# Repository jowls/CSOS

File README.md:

# csos

Current sink PCB for battery testing. Designed in KiCad. Includes circuit simulation (LTspice) and GERBER manufacturing files (configured for OSH Park fab). Studying Contextual Electronics courseware.

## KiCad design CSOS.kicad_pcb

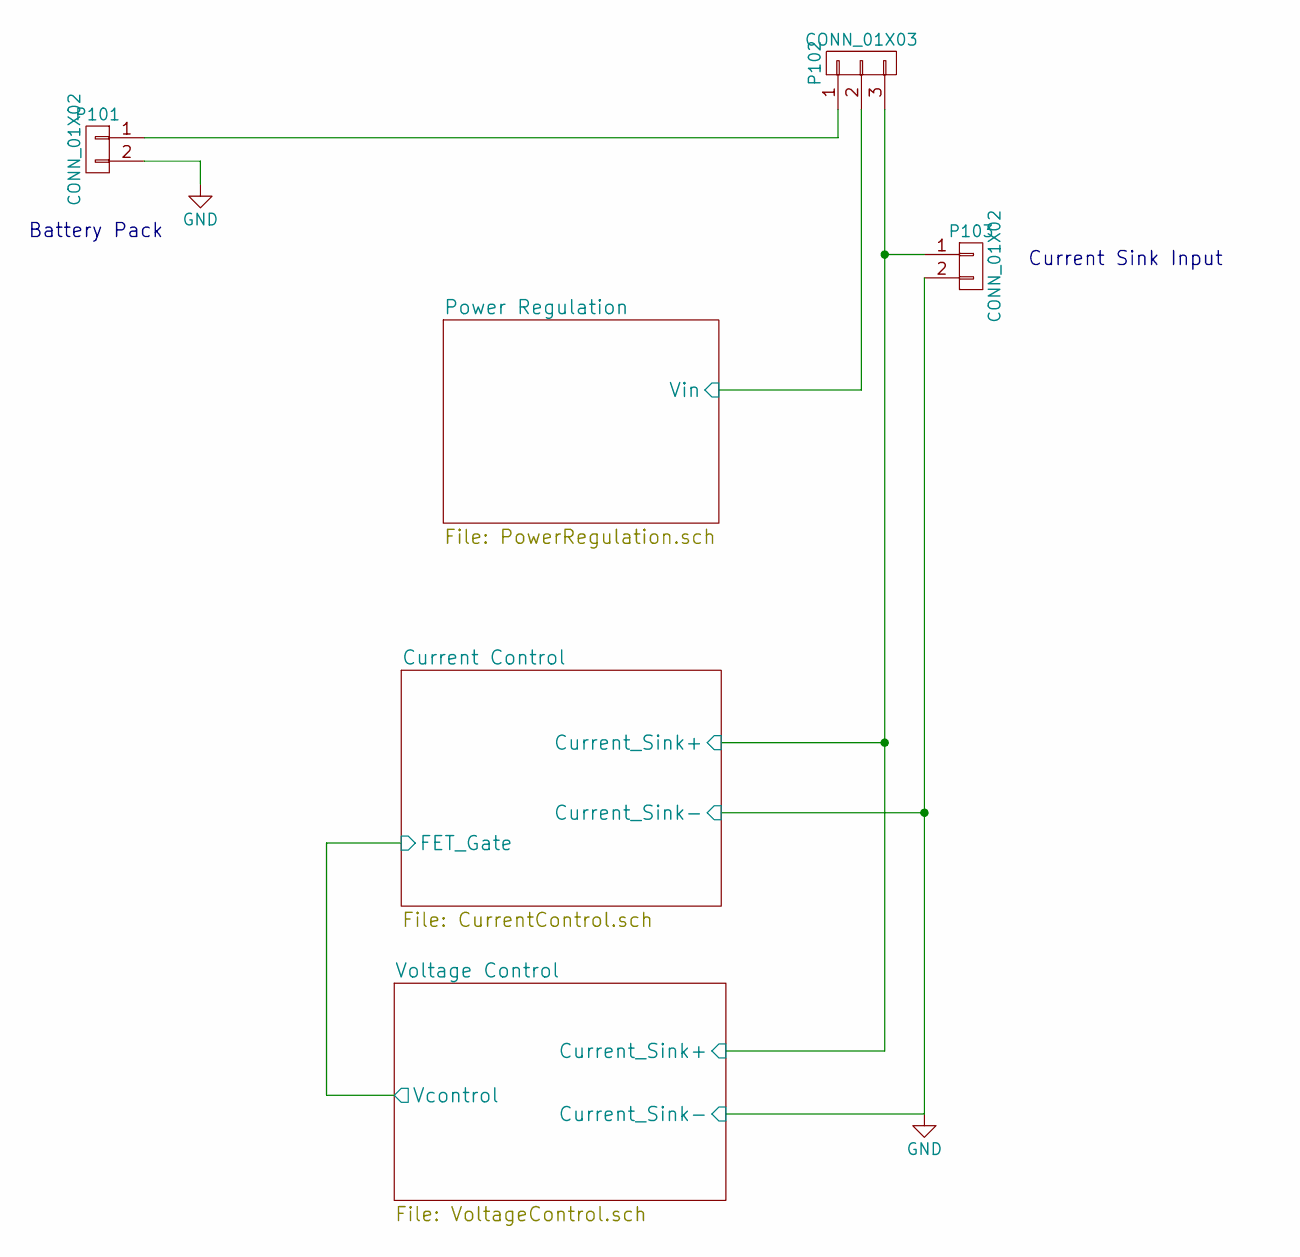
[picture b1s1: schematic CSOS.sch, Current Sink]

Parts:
P101, P103: CONN_01X02; Terminal_Block_200_mil; MPN OSTTC022162
P102: CONN_01X03; Pin_Header_Straight_1x03; MPN M20-9990346

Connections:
/Current Control/Current_Sink+: P102.3, P103.1; also elsewhere on the board
/Power Regulation/Vin: P102.2; also elsewhere on the board
GND: P101.2, P103.2; also elsewhere on the board
unnamed: P101.1, P102.1

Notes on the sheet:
Battery Pack
Current Sink Input

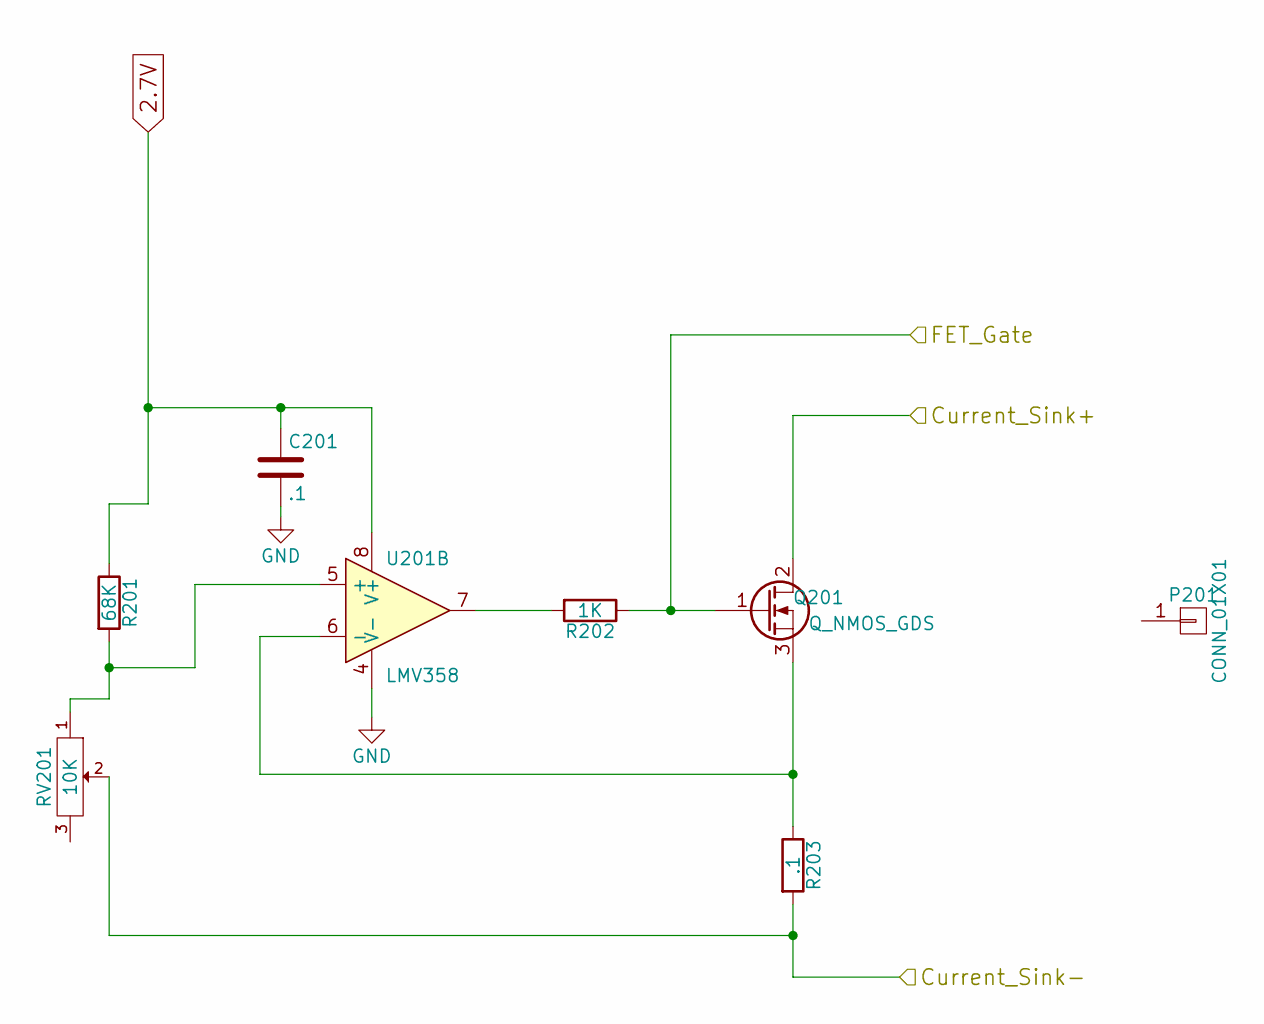
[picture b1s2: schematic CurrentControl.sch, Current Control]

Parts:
C201: .1; C_0805_HandSoldering; MPN 08055C104KAT2A
P201: CONN_01X01; FA-T220-38E; MPN FA-T220-38E
Q201: Q_NMOS_GDS; TO-220_Neutral123_Vertical; MPN PHP23NQ11T,127
R201: 68K; R_0805_HandSoldering
R202: 1K; R_0805_HandSoldering
R203: .1; Resistor_Horizontal_RM15mm; MPN AC01000001007JA100
RV201: 10K; P090L-02F25BR10K; MPN P090L-02F25BR10K
U201: LMV358; SOIC-8-N; MPN LMV358IDT

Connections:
2.7V: C201.1, R201.1, U201.8 (V+); also elsewhere on the board
/Current Control/Current_Sink+: Q201.2 (D); also elsewhere on the board
/Current Control/FET_Gate: Q201.1 (G), R202.1; also elsewhere on the board
GND: C201.2, R203.2, RV201.2, U201.4 (V-); also elsewhere on the board
unnamed: Q201.3 (S), R203.1, U201.6 (-)
unnamed: R201.2, RV201.1, U201.5 (+)
unnamed: R202.2, U201.7

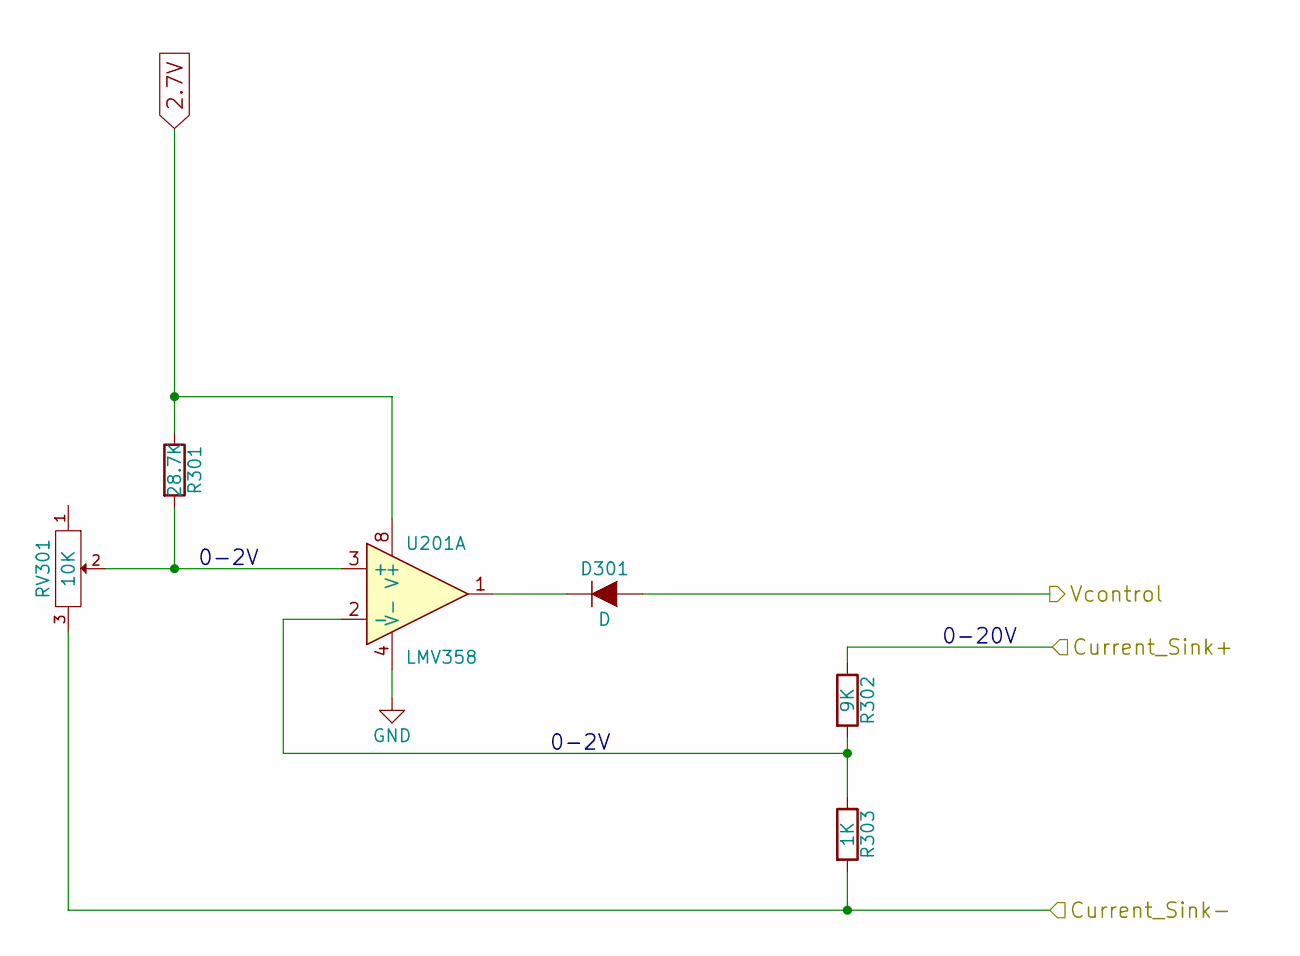
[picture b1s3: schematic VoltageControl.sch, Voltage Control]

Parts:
D301: D; SOD-123; MPN 1N4148W-7-F
R301: 28.7K; R_0805_HandSoldering
R302: 9K; R_0805_HandSoldering
R303: 1K; R_0805_HandSoldering
RV301: 10K; P090L-02F25BR10K
U201: LMV358; SOIC-8-N

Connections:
2.7V: R301.1, U201.8 (V+); also elsewhere on the board
/Current Control/Current_Sink+: R302.1; also elsewhere on the board
/Current Control/FET_Gate: D301.2 (A); also elsewhere on the board
GND: R303.2, RV301.3, U201.4 (V-); also elsewhere on the board
unnamed: D301.1 (K), U201.1
unnamed: R301.2, RV301.2, U201.3 (+)
unnamed: R302.2, R303.1, U201.2 (-)

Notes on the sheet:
0-2V
0-20V

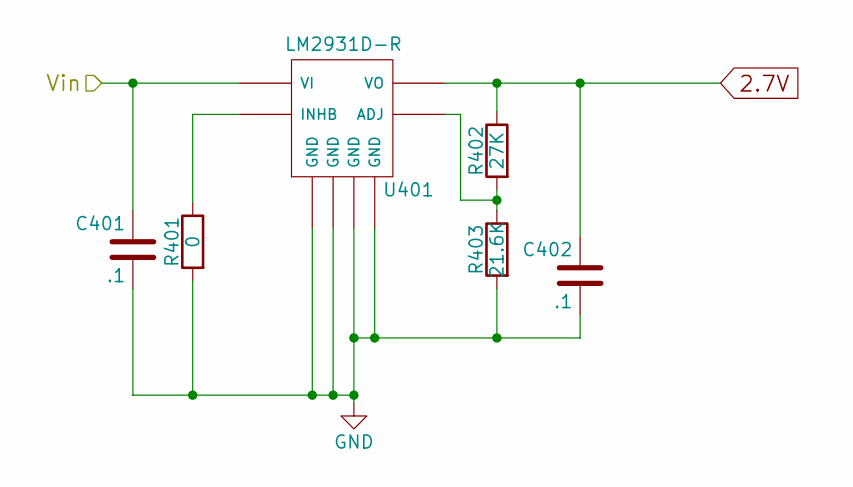
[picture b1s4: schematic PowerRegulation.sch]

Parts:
C401, C402: .1; C_0805_HandSoldering; MPN 08055C104KAT2A
R401: 0; R_0805_HandSoldering
R402: 27K; R_0805_HandSoldering
R403: 21.6K; R_0805_HandSoldering
U401: LM2931D-R; SOIC-8-N; MPN LM2931D-R

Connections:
2.7V: C402.1, R402.1, U401.1 (VO); also elsewhere on the board
/Power Regulation/Vin: C401.1, U401.8 (VI); also elsewhere on the board
GND: C401.2, C402.2, R401.2, R403.2, U401.2 (GND), U401.3 (GND), U401.6 (GND), U401.7 (GND); also elsewhere on the board
unnamed: R401.1, U401.5 (INHB)
unnamed: R402.2, R403.1, U401.4 (ADJ)

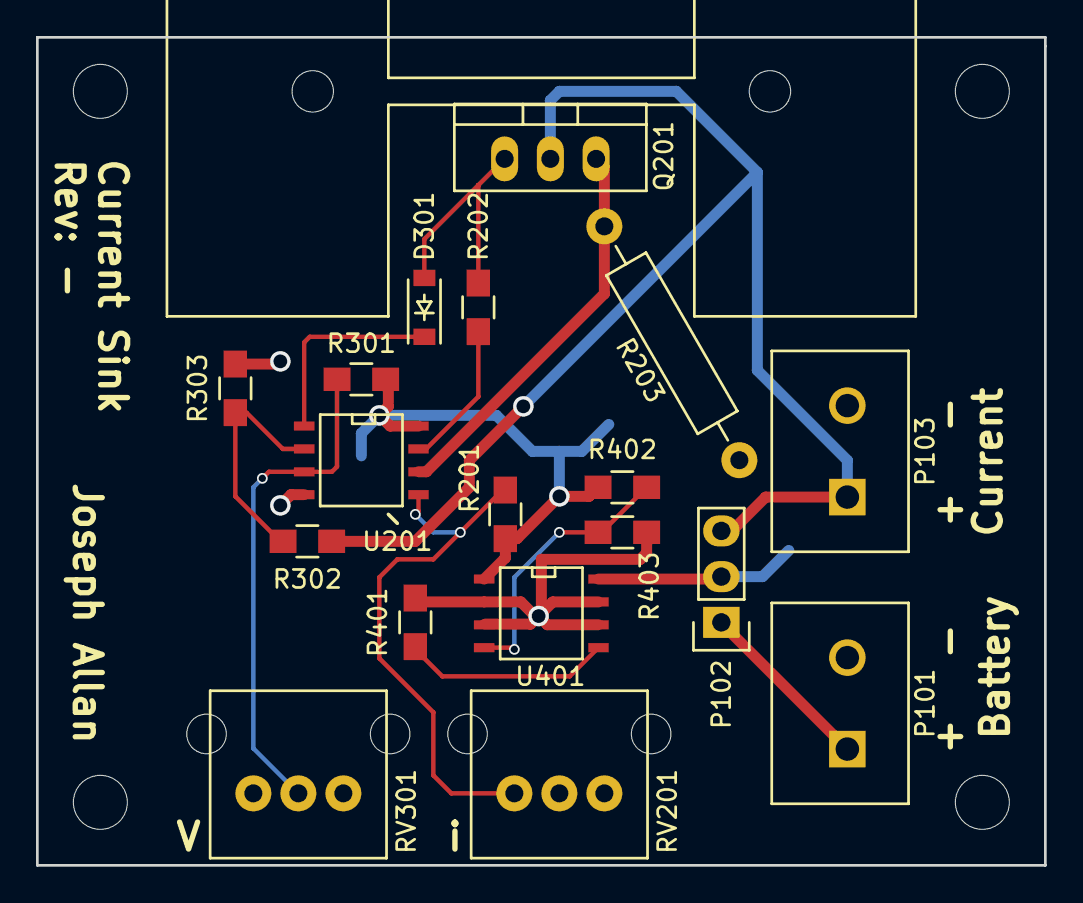
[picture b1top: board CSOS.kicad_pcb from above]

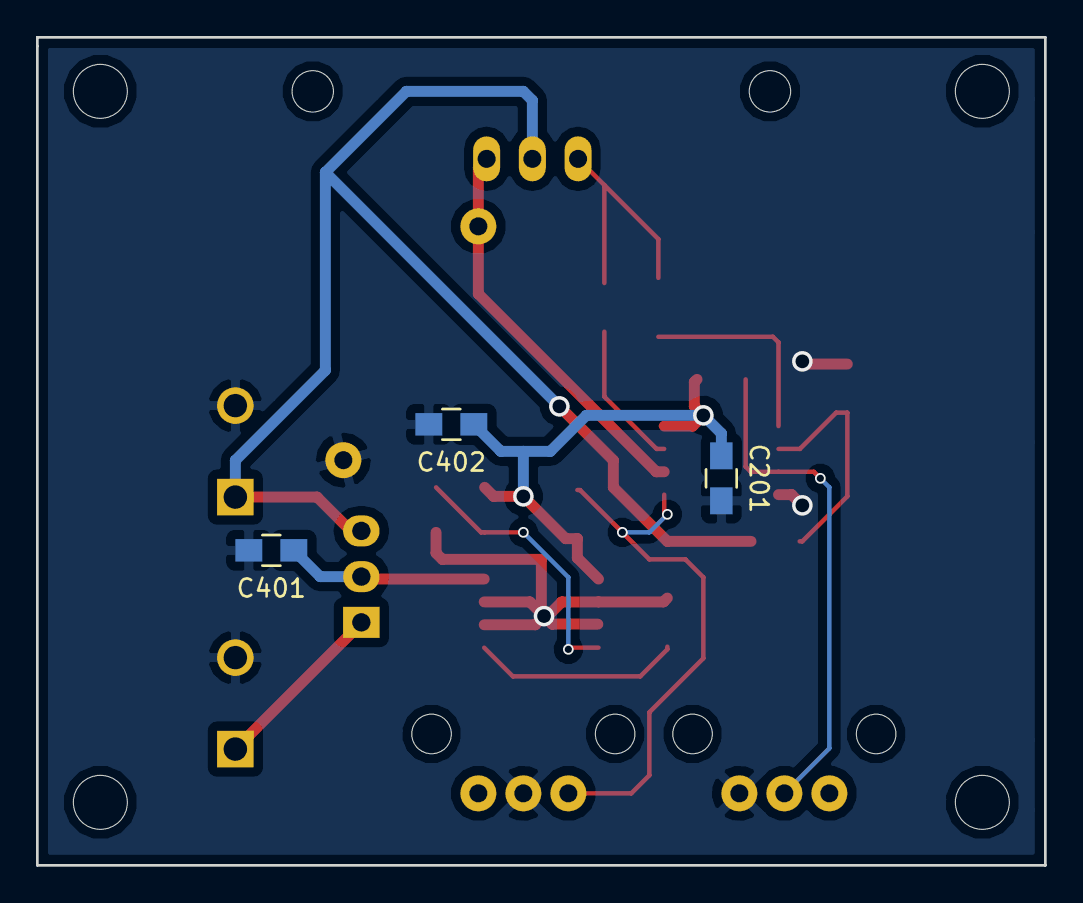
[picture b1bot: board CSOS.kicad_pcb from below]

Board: 2 copper layers, 56.0 x 46.0 mm, 22 parts (3 on the bottom side), 14 nets.

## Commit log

2016-05-23 Create project and schematic
2016-05-26 Initial schematic without component values.
2016-05-28 Updating the schematic with part numbers.
2016-05-30 Upgrading linear regulator.
2016-06-11 Adding FET power SPICE sim.
2016-06-12 Adding hierarchical sheets and voltage regulation circuit.
2016-06-12 Initial annotation.
2016-06-13 Initial component association and global spread in layout.
2016-06-13 Creating heatsink footprint and adding to schematic and layout.
2016-06-14 Built 200 mil pitch terminal block. Updated pcb layout with new footprints.
2016-06-15 Built potentiometer and added to layout.
2016-06-15 Fixing voltage dividers and adding values.
2016-06-15 Starting parts placement.
2016-06-16 Fixing FET.
2016-06-16 Layout connected.
2016-06-16 Gerber generation.
2016-06-16 Gerbers sent to OSH Park.
2016-06-19 Finalizing MPNs and passive values for BOM generation and ordering parts.
2016-06-20 Updating FET MPN.
